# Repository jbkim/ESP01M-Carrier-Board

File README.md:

# ESP-01M Carrier Board

### ESP-01M 모듈

[ESP8285](./datasheet/ESP8285_Datasheet_EN.pdf) 기반의 모듈임.

### ESP-01M Carrier Board

브레드 보드에 장착할 수 있다.

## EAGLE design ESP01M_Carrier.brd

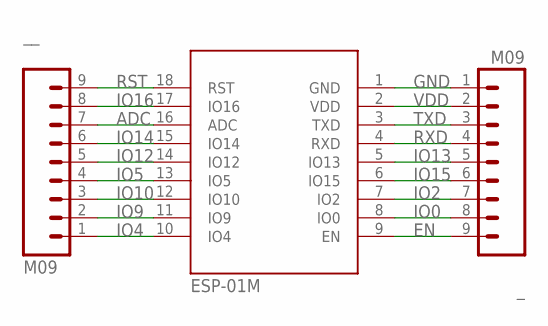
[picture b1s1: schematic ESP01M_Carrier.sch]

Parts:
ESP-01M: ESP-01M
_: M09; 1X09
__: M09; 1X09

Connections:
ADC: ESP-01M.16 (ADC), __.7
EN: ESP-01M.9 (EN), _.9
GND: ESP-01M.1 (GND), _.1
IO0: ESP-01M.8 (IO0), _.8
IO2: ESP-01M.7 (IO2), _.7
IO4: ESP-01M.10 (IO4), __.1
IO5: ESP-01M.13 (IO5), __.4
IO9: ESP-01M.11 (IO9), __.2
IO10: ESP-01M.12 (IO10), __.3
IO12: ESP-01M.14 (IO12), __.5
IO13: ESP-01M.5 (IO13), _.5
IO14: ESP-01M.15 (IO14), __.6
IO15: ESP-01M.6 (IO15), _.6
IO16: ESP-01M.17 (IO16), __.8
RST: ESP-01M.18 (RST), __.9
RXD: ESP-01M.4 (RXD), _.4
TXD: ESP-01M.3 (TXD), _.3
VDD: ESP-01M.2 (VDD), _.2

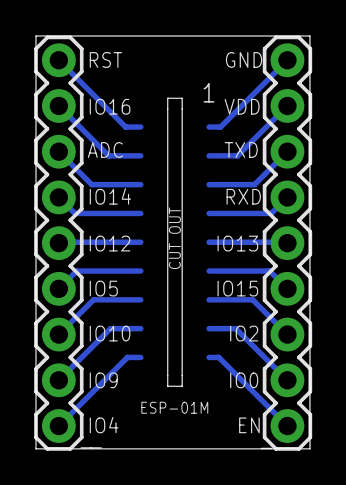
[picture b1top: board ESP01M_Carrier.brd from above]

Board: 2 copper layers, 15.2 x 22.9 mm, 3 parts (0 on the bottom side), 18 nets.

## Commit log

2018-08-17 uipdate gerber & pcb layout
2018-08-17 update omage

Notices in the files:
parts and their libraries:
SparkFun: Licensing: CC v3.0 Share-Alike You are welcome to use this library for commercial purposes.
